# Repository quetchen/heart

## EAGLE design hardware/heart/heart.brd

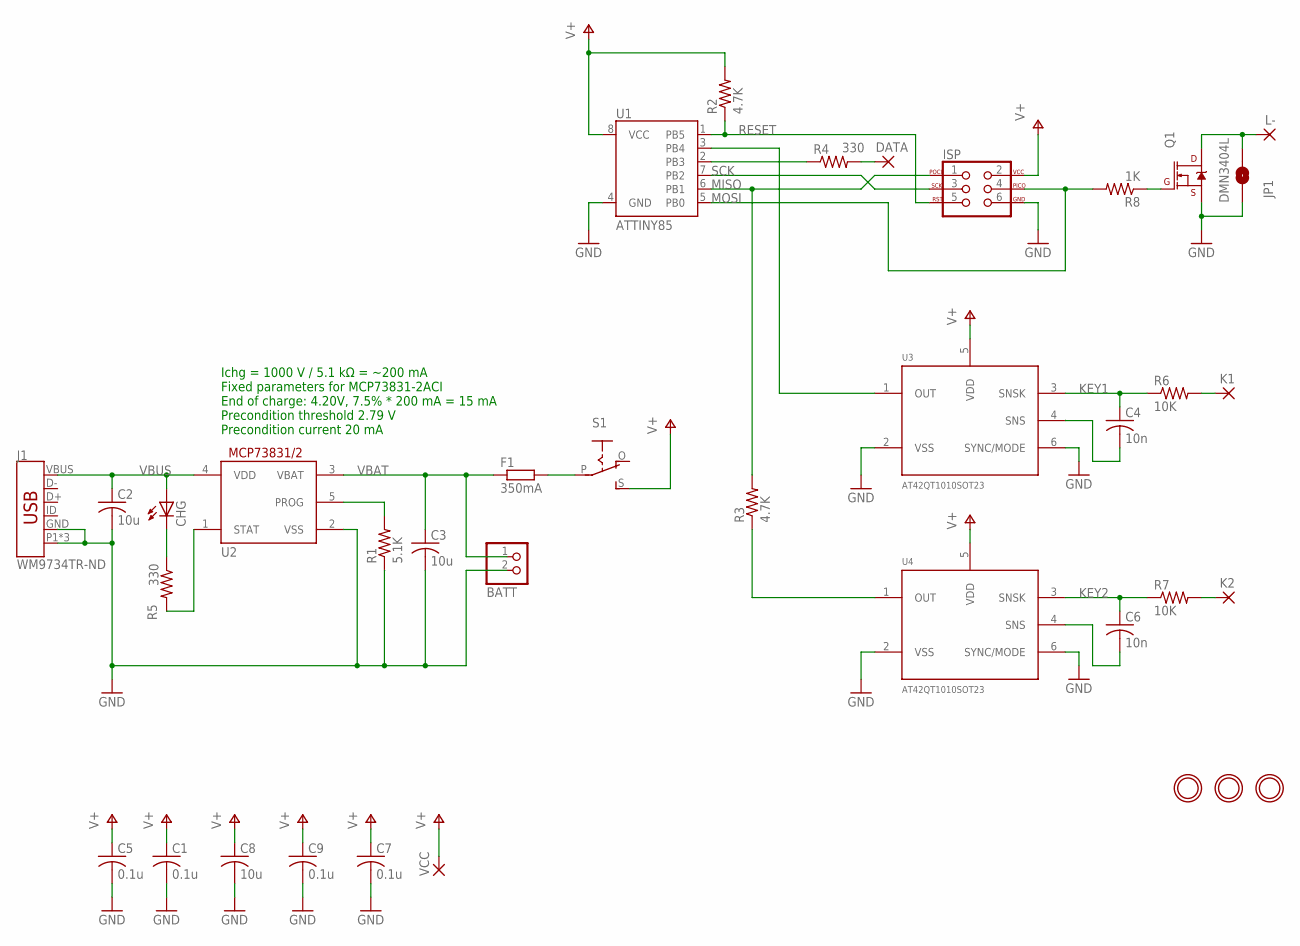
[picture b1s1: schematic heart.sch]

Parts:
BATT: JST_2PIN-THM-RA; JST-PH-2-THM-RA
C1, C5, C7, C9: 0.1u; C0603
C2, C3, C8: 10u; C0603
C4, C6: 10n; C0603
CHG: LEDCHIP-LED0805; CHIP-LED0805
DATA: 2,15/1,0
F1: 350mA; R0603
ISP: AVR_SPI_PROG_3X2PTH; 2X3
J1: WM9734TR-ND; USB-B-MICRO-SMD_VERT
JP1: JUMPER-SMT_2_NO_NO-SILK; SMT-JUMPER_2_NO_NO-SILK
K1, K2: 2,15/1,0
L-: 2,15/1,0
Q1: DMN3404L; SOT23-3
R1: 5.1K; R0603
R2, R3: 4.7K; R0603
R4, R5: 330; R0603
R6, R7: 10K; R0603
R8: 1K; R0603
S1: EG1218S; EG1218
U1: ATTINY85
U2: MCP73831/OT; SOT23-5L
U3, U4: AT42QT1010SOT23; SOT23-6
U$1, U$2, U$4: MICROBUILDER_MOUNTINGHOLE2.0; MICROBUILDER_MOUNTINGHOLE_2.0_PLATED
VCC: 1,6/0,9

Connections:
GND: BATT.2 (1), C1.2, C2.2, C3.2, C5.2, C7.2, C8.2, C9.2, ISP.6, J1.GND, J1.P1 (SHIELD), J1.P2 (SHIELD), J1.P3 (SHIELD), JP1.1, Q1.2 (S), R1.1, U1.4 (GND), U2.2 (VSS), U3.2 (VSS), U3.6 (SYNC/MODE), U4.2 (VSS), U4.6 (SYNC/MODE)
KEY1: C4.1, R6.1, U3.3 (SNSK)
KEY2: C6.1, R7.1, U4.3 (SNSK)
KOUT1: U1.3 (PB4), U3.1 (OUT)
KOUT2: R3.1, U4.1 (OUT)
LED_DATA: DATA.1, R4.2
LED_PIN: R4.1, U1.2 (PB3)
MISO: ISP.1, R3.2, U1.6 (PB1)
MOSI: ISP.4, R8.2, U1.5 (PB0)
unnamed: F1.2, S1.P
unnamed: K1.1, R6.2
unnamed: K2.1, R7.2
unnamed: C4.2, U3.4 (SNS)
unnamed: JP1.2, L-.1, Q1.3 (D)
unnamed: Q1.1 (G), R8.1
unnamed: CHG.C, R5.1
unnamed: C6.2, U4.4 (SNS)
PROG: R1.2, U2.5 (PROG)
RESET: ISP.5, R2.1, U1.1 (PB5)
SCK: ISP.3, U1.7 (PB2)
STAT: R5.2, U2.1 (STAT)
V+: C1.1, C5.1, C7.1, C8.1, C9.1, ISP.2, R2.2, S1.S, U1.8 (VCC), U3.5 (VDD), U4.5 (VDD), VCC.1
VBAT: BATT.1 (2), C3.1, F1.1, U2.3 (VBAT)
VBUS: C2.1, CHG.A, J1.VBUS, U2.4 (VDD)

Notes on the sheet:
Ichg = 1000 V / 5.1 kΩ = ~200 mA Fixed parameters for MCP73831-2ACI End of charge: 4.20V, 7.5% * 200 mA = 15 mA Precondition threshold 2.79 V Precondition current 20 mA

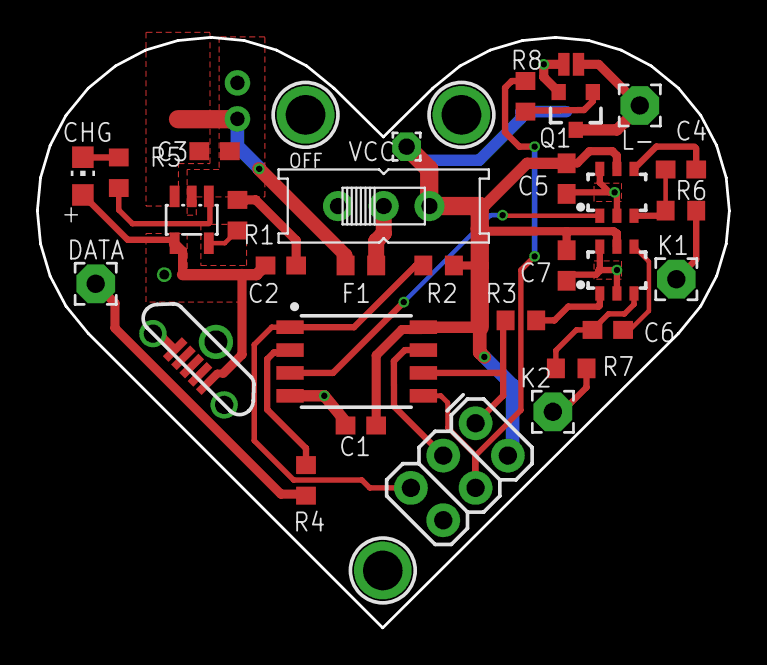
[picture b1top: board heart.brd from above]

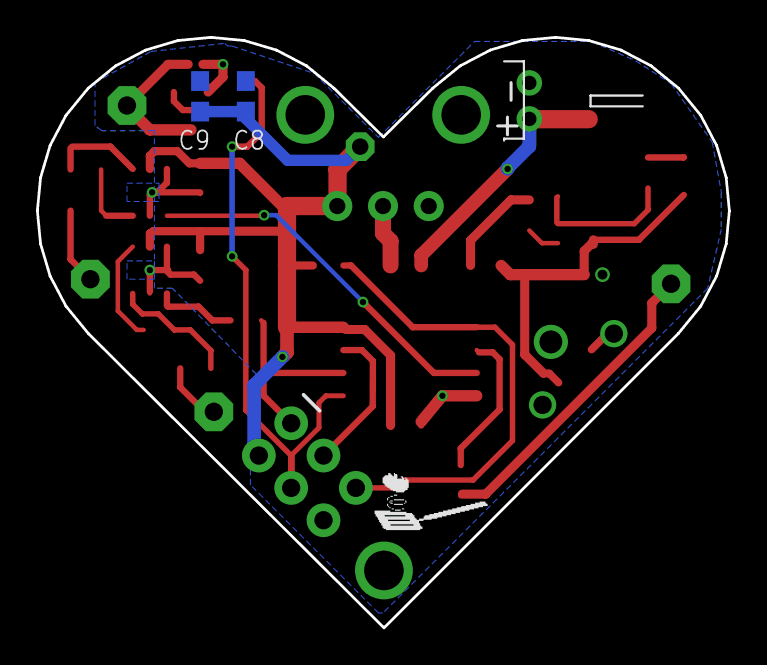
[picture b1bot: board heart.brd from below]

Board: 2 copper layers, 38.4 x 32.8 mm, 37 parts (3 on the bottom side), 24 nets.

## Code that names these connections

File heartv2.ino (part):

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
//#define ELEPHANT

#define LED_PIN PIN_PB3
#define TOUCH_PIN1 PIN_PB4
#define TOUCH_PIN2 PIN_PB1

#define LED_POWER_ENABLE PIN_PB0

#ifdef ELEPHANT
#define BUTTON_PRESSED LOW
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  pinMode(TOUCH_PIN1, INPUT_PULLUP);
  pinMode(TOUCH_PIN2, INPUT_PULLUP);
  pinMode(SCK, INPUT);
  // for the elephant, PB0 is an input that gets grounded
  // when the charger is connected
  pinMode(PIN_PB0, INPUT_PULLUP);
#else
  pinMode(TOUCH_PIN1, INPUT);
  pinMode(TOUCH_PIN2, INPUT);
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  lock_buttons = EEPROM.read(EEPROM_LOCKED);

  FastLED.setBrightness(BRIGHT_INIT);
  FastLED.addLeds<WS2812B, LED_PIN>(leds, LED_COUNT);
  FastLED.setCorrection(Typical8mmPixel);

  // turn on the timer 0 output compare A interrupt
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
    if (!uvlo && (volt_rdg > UVLO_ENGAGE || EEPROM.read(EEPROM_UVLO)
#ifdef ELEPHANT
       || digitalRead(PIN_PB0)==LOW

#endif     
      )){
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      FastLED.clear(true);

      // if we don't do this the LEDs will still be able to sink current through the data input
      pinMode(LED_PIN, INPUT);

      // now disable LED power
#ifndef ELEPHANT
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
    } else if (uvlo && volt_rdg < UVLO_RELEASE
#ifdef ELEPHANT
      && digitalRead(PIN_PB0) == HIGH
#endif
    ){
      uvlo = false;
      pinMode(LED_PIN, OUTPUT);
#ifndef ELEPHANT
      digitalWrite(LED_POWER_ENABLE, HIGH);
#endif
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
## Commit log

2024-12-16 Add files via upload
    Initial commit
2024-12-16 disable elephant target; add comment
2024-12-16 add hardware schematics

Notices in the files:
parts and their libraries:
SparkFun-IC-Microcontroller: Licensing: Creative Commons ShareAlike 4.0 International - https://creativecommons.org/licenses/by-sa/4.0
